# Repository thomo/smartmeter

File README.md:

# SmartMeter Gateway

A complete hardware solution for reading data from smart energy meters via their optical interface. This project provides the PCB designs for an IR read/write head and an ESP8266-based controller board designed to run **Tasmota**.

## Overview

The SmartMeter Gateway consists of two primary components:
1.  **IR Read/Write Head**: An optical probe that attaches to the smart meter's IR port.
2.  **ESP8266 Controller Board**: A carrier board for an ESP8266 module (e.g., ESP-12F) that processes the IR signals and provides a network interface via Wi-Fi.

By running Tasmota on the ESP8266, the meter data can be easily integrated into Home Automation systems like **Home Assistant**, **OpenHAB**, or **ioBroker** using MQTT or REST API.

## Hardware

The PCB designs are located in the `board` directory. These files were created with Autocad Eagle.

### 1. IR Read/Write Head (`board/ir_rw_head`)
The IR head is responsible for the physical communication with the energy meter.
- **Schematic**: [ir_rw_head_circuit.pdf](board/ir_rw_head_circuit.pdf)
- **Files**: Eagle schematic (`.sch`) and PCB layout (`.brd`).
- **Visuals**: 
    - [Top View](board/ir_rw_head_pcb_top.png)
    - [Bottom View](board/ir_rw_head_pcb_bottom.png)

### 2. ESP8266 Controller Board (`board/smartmeter`)
The main board that houses the ESP8266 and connects to the IR head.
- **Schematic**: [smartmeter_circuit.pdf](board/smartmeter_circuit.pdf)
- **Files**: Eagle schematic (`.sch`) and PCB layout (`.brd`).
- **Visuals**:
    - [Top View](board/smartmeter_pcb_top.png)
    - [Bottom View](board/smartmeter_pcb_bottom.png)

## Software / Firmware

The board is designed to be used with the [Tasmota](https://tasmota.github.io/docs/) firmware.

### Configuration
1. Build a customized tasmota image with SML/OBIS support 
   - see [Tasmota Smart Meter Interface](https://tasmota.github.io/docs/Smart-Meter-Interface/)
   - see [HOW TO: TASMOTA SML](https://docs.google.com/document/d/1olSGZcaE_vkdNXzN_p0zGee61xKCcK3HJe3Al00xj2g/edit?usp=sharing).
2. Configure the GPIOs for the IR receiver and transmitter.
```tasmota  
{"NAME":"Smartmeter","GPIO":[1,1,1,1,1,1,1,1,0,0,1,1,1,0],"FLAG":0,"BASE":18}
```

3. Use a Tasmota Script (SML) to decode the specific data format of your energy meter (e.g., SML or OBIS) - do not forget to enable the "Enable Script" checkbox. 

Example Tasmota SML script snippet:
```tasmota
>D

>B
=>sensor53 r
>M 2
+1,13,s,0,9600,Haus
+2,12,s,0,9600,PV

;1,77070100100700FF@1,Aktuell,W,Power_curr,0
1,77070100010800FF@1000,Bezug,kWh,Tariflos,2
1,77070100020800FF@1000,Einspeisung,kWh,Tariflos,2
2,=h============
;2,77070100100700FF@1,Aktuell,W,Power_curr,0
2,77070100010800FF@1000,Verbrauch,kWh,Tariflos,2
2,77070100020800FF@1000,Produktion,kWh,Tariflos,2
#
```

## Assembly

Detailed images of the assembled boards can be found in the `images` folder.
- [Inside View](images/SmartMeter_inside.jpeg)

## License

Standard open-source licenses apply. See design files for details.

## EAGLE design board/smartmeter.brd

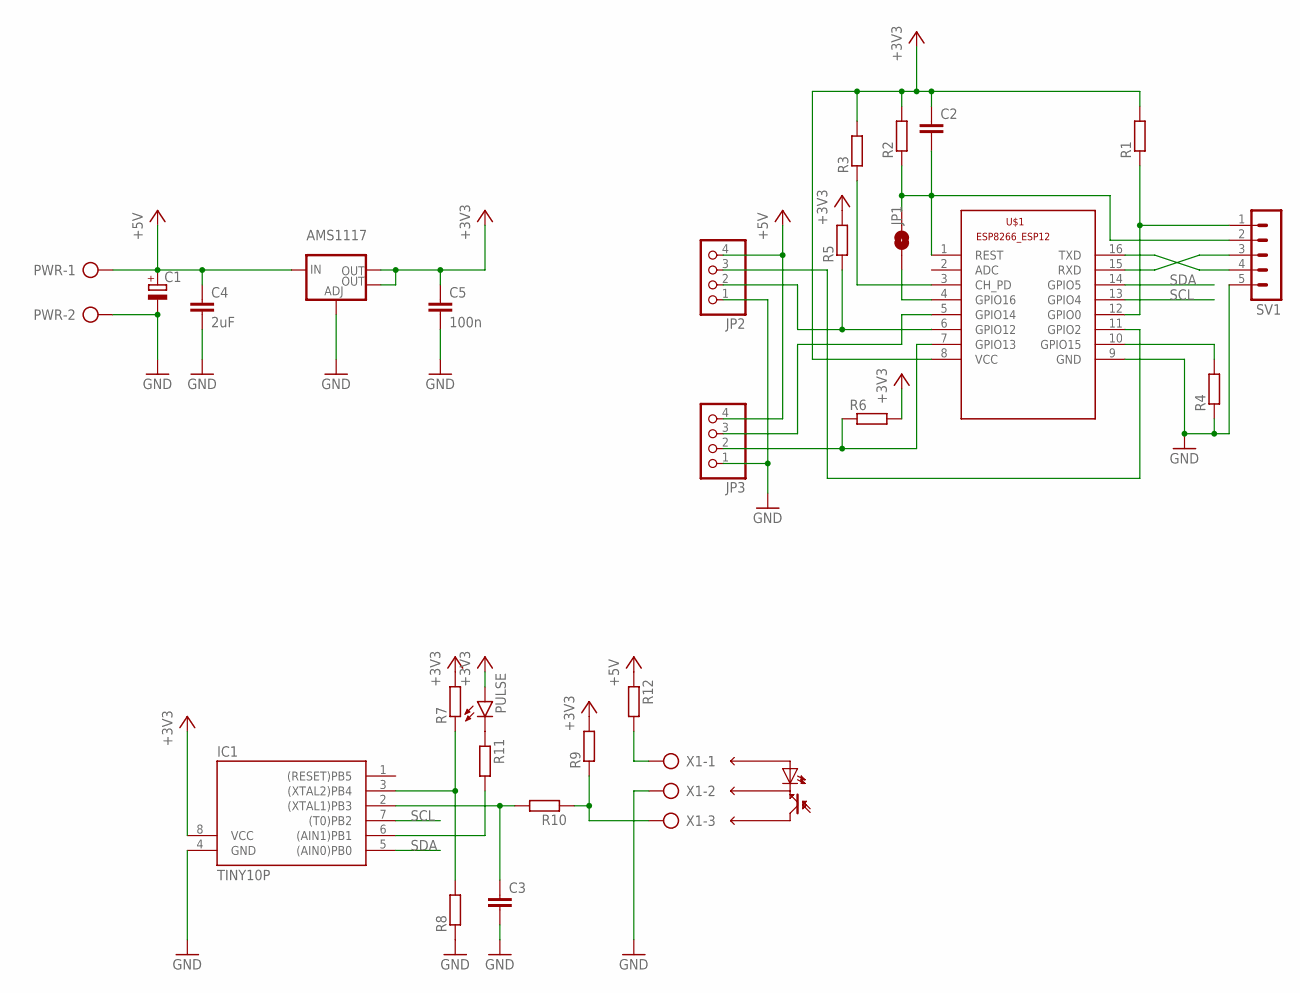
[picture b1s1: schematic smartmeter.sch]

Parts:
AMS1117: V_REG_LM1117SOT223; SOT223
C1: CPOL-EUE3.5-10; E3,5-10
C2, C3: C-EU050-025X075; C050-025X075
C4: 2uF; C025-025X050
C5: 100n; C025-025X050
IC1: TINY10P; DIL08
JP1: JUMPER-SMT_2_NO_SILK; SMT-JUMPER_2_NO_SILK
JP2, JP3: PINHD-1X4/90; 1X04/90
PULSE: LED5MM
PWR: AK500/2
R1, R2, R3, R4, R5, R6, R7, R8, R9, R10, R11, R12: R-EU_0207/10; 0207/10
SV1: MA05-1
U$1: ESP8266-12; ESP8266-ESP12
X1: AK500/3

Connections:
+3V3: AMS1117.2 (OUT), AMS1117.4 (OUT), C2.1, C5.1, IC1.8 (VCC), PULSE.A, R1.2, R2.2, R3.2, R5.2, R6.2, R7.2, R9.2, U$1.8 (VCC)
+5V: AMS1117.3 (IN), C1.+, C4.1, JP2.4, JP3.4, PWR.1, R12.1
GND: AMS1117.1 (ADJ), C1.-, C3.2, C4.2, C5.2, IC1.4 (GND), JP2.1, JP3.1, PWR.2, R4.1, R8.1, SV1.5, U$1.9 (GND), X1.2
unnamed: R1.1, SV1.1, U$1.12 (GPIO0)
unnamed: C2.2, JP1.2, R2.1, SV1.2, U$1.1 (REST)
unnamed: R4.2, U$1.10 (GPIO15)
unnamed: JP1.1, U$1.4 (GPIO16)
unnamed: R3.1, U$1.3 (CH_PD)
unnamed: SV1.4, U$1.16 (TXD)
unnamed: SV1.3, U$1.15 (RXD)
unnamed: C3.1, IC1.2 ((XTAL1)PB3), R10.2
unnamed: IC1.3 ((XTAL2)PB4), R7.1, R8.2
unnamed: JP2.3, U$1.11 (GPIO2)
unnamed: JP2.2, R5.1, U$1.6 (GPIO12)
unnamed: JP3.3, U$1.5 (GPIO14)
unnamed: JP3.2, R6.1, U$1.7 (GPIO13)
unnamed: R9.1, R10.1, X1.3
unnamed: IC1.6 ((AIN1)PB1), R11.2
unnamed: PULSE.K (C), R11.1
unnamed: R12.2, X1.1
SCL: IC1.7 ((T0)PB2), U$1.13 (GPIO4)
SDA: IC1.5 ((AIN0)PB0), U$1.14 (GPIO5)

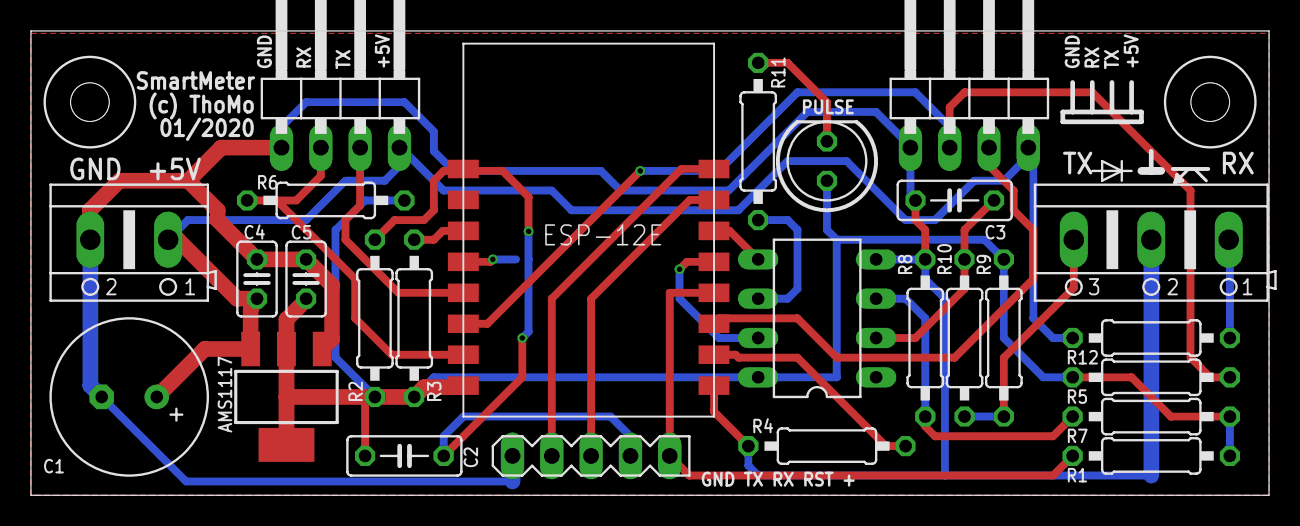
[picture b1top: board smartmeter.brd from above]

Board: 2 copper layers, 80.0 x 30.0 mm, 29 parts (1 on the bottom side), 22 nets.

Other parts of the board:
U$2, U$3: DRIL-2,5

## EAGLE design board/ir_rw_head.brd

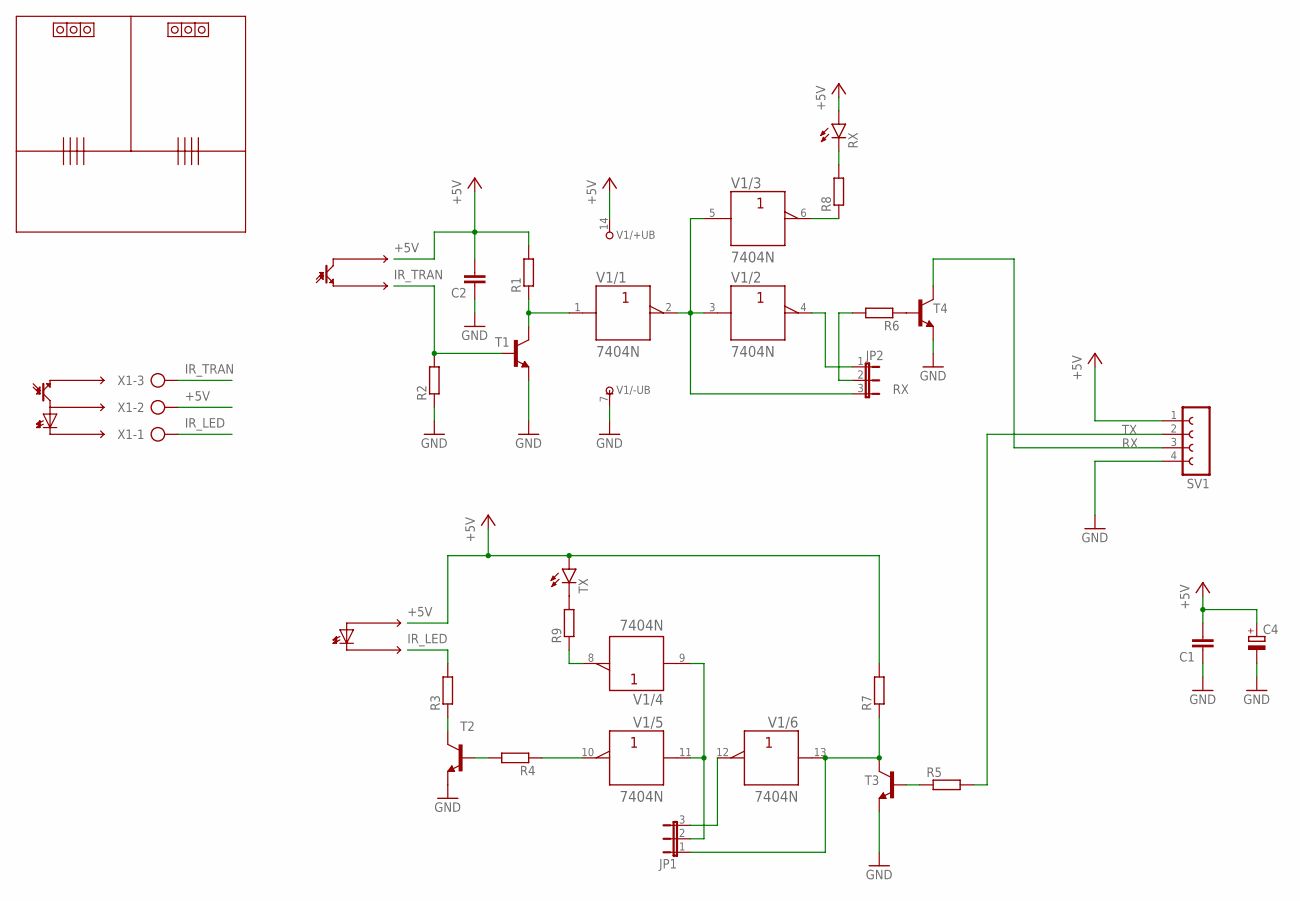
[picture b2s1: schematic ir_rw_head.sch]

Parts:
C1, C2: C-EU050-030X075; C050-030X075
C4: CPOL-EUE2.5-7; E2,5-7
JP1, JP2: JP2E; JP2
R1, R2, R3, R4, R5, R6, R7, R8, R9: R-EU_0207/10; 0207/10
RX: LED5MM
SV1: FE04-1W
T1, T2, T3, T4: -NPN-TO92-EBC; TO92-EBC
TX: LED5MM
V1: 7404N; DIL14
X1: AK500/3

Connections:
+5V: C1.2, C2.2, C4.+, R1.2, R7.2, RX.A, SV1.1, TX.A, V1.14 (+UB), X1.2
GND: C1.1, C2.1, C4.-, R2.1, SV1.4, T1.E, T2.E, T3.E, T4.E, V1.7 (-UB)
IR_LED: R3.2, X1.1
IR_TRAN: R2.2, T1.B, X1.3
unnamed: R4.2, T2.B
unnamed: R3.1, T2.C
unnamed: R4.1, V1.10 (Y)
unnamed: JP1.1, R7.1, T3.C, V1.13 (A)
unnamed: R5.1, T3.B
unnamed: R8.2, RX.K (C)
unnamed: R1.1, T1.C, V1.1 (A)
unnamed: JP2.3, V1.2 (Y), V1.3 (A), V1.5 (A)
unnamed: R9.2, TX.K (C)
unnamed: R6.1, T4.B
unnamed: JP2.2, R6.2
unnamed: JP2.1, V1.4 (Y)
unnamed: R8.1, V1.6 (Y)
unnamed: R9.1, V1.8 (Y)
unnamed: JP1.3, V1.12 (Y)
RX: SV1.3, T4.C
TX: R5.2, SV1.2
TX_L: JP1.2, V1.9 (A), V1.11 (A)

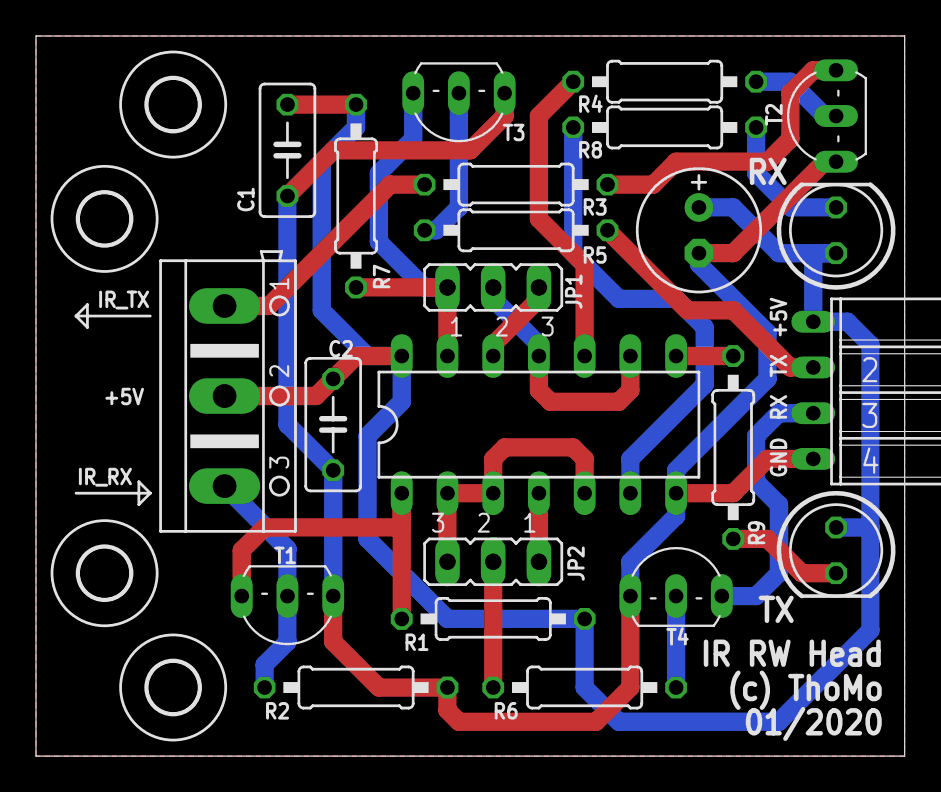
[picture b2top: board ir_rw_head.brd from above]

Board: 2 copper layers, 48.3 x 40.0 mm, 27 parts (0 on the bottom side), 22 nets.

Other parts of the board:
U$1, U$2, U$3, U$4: 2,8

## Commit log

2020-01-18 PCB IR header and master
2020-01-23 set frame vars and add pictures
2020-01-23 init board code
2020-01-23 remove wrong code
2020-01-23 update DRC rules
2026-01-01 add README

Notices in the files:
parts and their libraries:
SparkFun-Aesthetics: Licensing: Creative Commons ShareAlike 4.0 International - https://creativecommons.org/licenses/by-sa/4.0
